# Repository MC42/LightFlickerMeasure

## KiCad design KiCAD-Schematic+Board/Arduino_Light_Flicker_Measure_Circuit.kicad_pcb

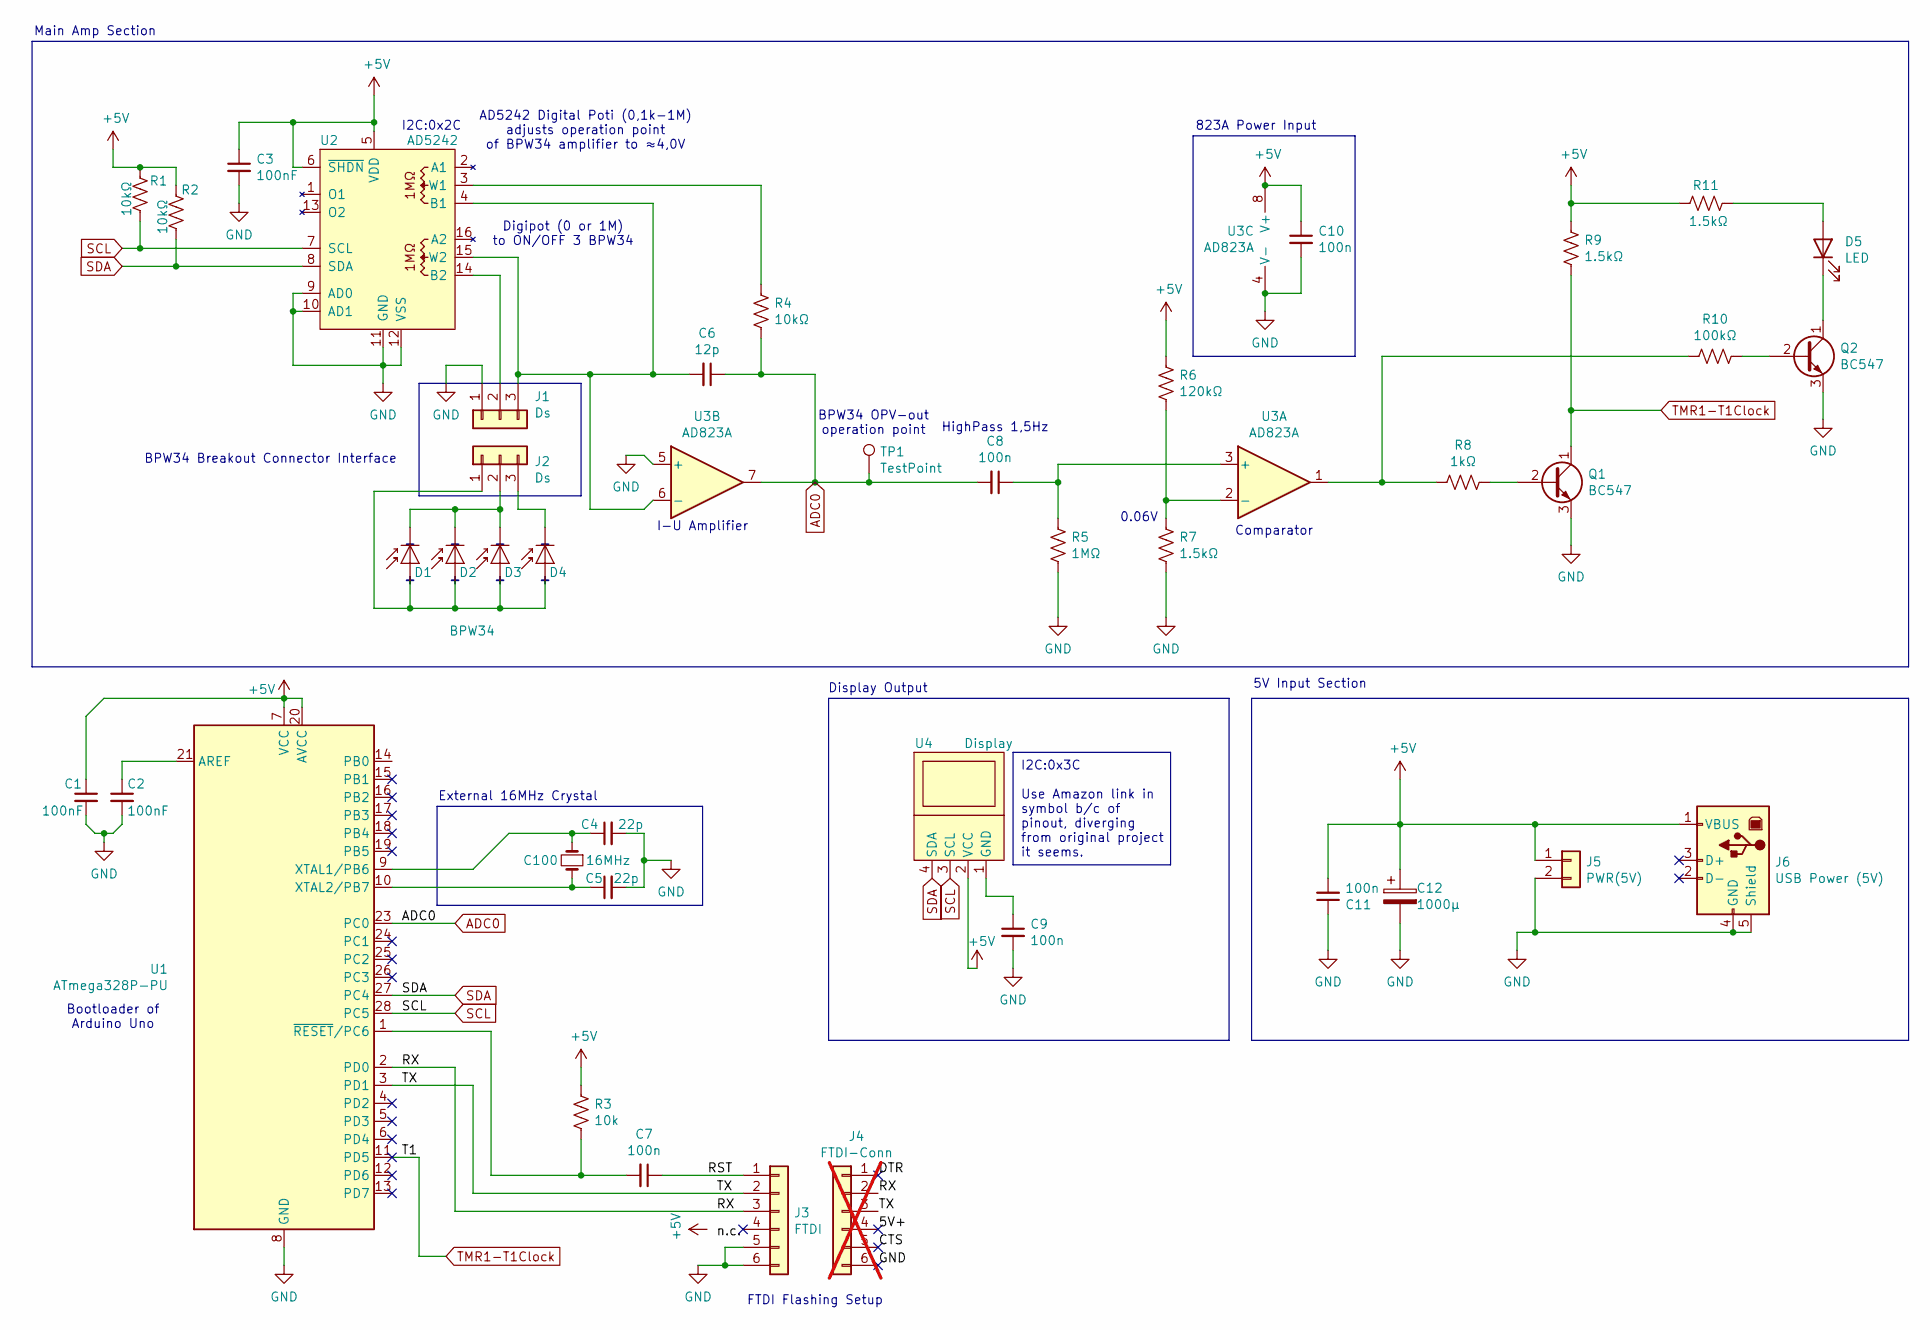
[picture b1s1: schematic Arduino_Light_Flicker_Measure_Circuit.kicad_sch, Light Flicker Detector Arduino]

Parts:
C1, C3: 100nF; C_Rect_L11.0mm_W2.8mm_P10.00mm_MKT
C2: 100nF; C_Rect_L4.0mm_W2.5mm_P2.50mm
C4, C5: 22p; C_Disc_D3.0mm_W1.6mm_P2.50mm
C6: 12p; C_Disc_D3.0mm_W1.6mm_P2.50mm
C7, C10: 100n; C_Rect_L9.0mm_W2.5mm_P7.50mm_MKT
C8: 100n; C_Rect_L7.0mm_W2.0mm_P5.00mm
C9, C11: 100n; C_Rect_L4.0mm_W2.5mm_P2.50mm
C12: 1000µ; CP_Radial_D8.0mm_P3.50mm
C100: 16MHz; Crystal_HC49-U_Vertical
D1, D2, D3, D4: BPW34; Osram_DIL2_4.3x4.65mm_P5.08mm
D5: LED; LED_D3.0mm
J1, J2: Ds; PinHeader_1x03_P2.54mm_Vertical
J3: FTDI; PinHeader_1x06_P2.54mm_Vertical
J4: FTDI-Conn; PinHeader_1x06_P2.54mm_Vertical; not fitted
J5: PWR(5V); PinHeader_1x02_P2.54mm_Vertical
J6: USB Power (5V); USB_A_CNCTech_1001-011-01101_Horizontal
Q1, Q2: BC547; TO-92_HandSolder
R1, R2: 10kΩ; R_Axial_DIN0207_L6.3mm_D2.5mm_P10.16mm_Horizontal
R3: 10k; R_Axial_DIN0207_L6.3mm_D2.5mm_P10.16mm_Horizontal
R4: 10kΩ; R_Axial_DIN0207_L6.3mm_D2.5mm_P10.16mm_Horizontal
R5: 1MΩ; R_Axial_DIN0207_L6.3mm_D2.5mm_P10.16mm_Horizontal
R6: 120kΩ; R_Axial_DIN0207_L6.3mm_D2.5mm_P10.16mm_Horizontal
R7, R9, R11: 1.5kΩ; R_Axial_DIN0207_L6.3mm_D2.5mm_P10.16mm_Horizontal
R8: 1kΩ; R_Axial_DIN0207_L6.3mm_D2.5mm_P10.16mm_Horizontal
R10: 100kΩ; R_Axial_DIN0207_L6.3mm_D2.5mm_P10.16mm_Horizontal
TP1: TestPoint; PinHeader_1x01_P2.54mm_Vertical
U1: ATmega328P-PU; DIP-28_W7.62mm
U2: AD5242; SOIC-16_3.9x9.9mm_P1.27mm
U3: AD823A; SOIC-8_3.9x4.9mm_P1.27mm
U4: Display; PinHeader_1x04_P2.54mm_Vertical

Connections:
+5V: C1.1, C3.1, C10.1, C11.2, C12.1, J5.1, J6.1 (VBUS), R1.1, R2.1, R3.1, R6.1, R9.1, R11.1, U1.7 (VCC), U1.20 (AVCC), U2.5 (VDD), U2.6 (~SHDN), U3.8 (V+), U4.2 (VCC)
/RST: C7.1, J3.1
/RX: J3.3, J4.2, U1.2 (PD0)
/TX: J3.2, J4.3, U1.3 (PD1)
ADC0: C6.1, C8.2, R4.2, TP1.1, U1.23 (PC0), U3.7
GND: C1.2, C2.2, C3.2, C4.2, C5.2, C9.2, C10.2, C11.1, C12.2, J1.1, J3.5, J3.6, J5.2, J6.4 (GND), J6.5 (Shield), Q1.3 (E), Q2.3 (E), R5.2, R7.2, U1.8 (GND), U1.22 (GND), U2.9 (AD0), U2.10 (AD1), U2.11 (GND), U2.12 (VSS), U3.4 (V-), U3.5 (+)
unnamed: D1.2 (A), D2.2 (A), D3.2 (A), D4.2 (A), J2.1
unnamed: D1.1 (K), D2.1 (K), D3.1 (K), J2.2
unnamed: D4.1 (K), J2.3
unnamed: D5.2 (A), R11.2
unnamed: D5.1 (K), Q2.1 (C)
unnamed: J1.2, U2.14 (B2)
unnamed: C6.2, J1.3, U2.4 (B1), U2.15 (W2), U3.6 (-)
unnamed: Q1.2 (B), R8.1
unnamed: Q2.2 (B), R10.1
unnamed: R8.2, R10.2, U3.1
unnamed: C2.1, U1.21 (AREF)
unnamed: C4.1, C100.1, U1.9 (XTAL1/PB6)
unnamed: C5.1, C100.2, U1.10 (XTAL2/PB7)
unnamed: C7.2, R3.2, U1.1 (~RESET/PC6)
unnamed: R4.1, U2.3 (W1)
unnamed: C8.1, R5.1, U3.3 (+)
unnamed: R6.2, R7.1, U3.2 (-)
unnamed: C9.1, U4.1 (GND)
SCL: R1.2, U1.28 (PC5), U2.7 (SCL), U4.3 (SCL)
SDA: R2.2, U1.27 (PC4), U2.8 (SDA), U4.4 (SDA)
TMR1-T1Clock: Q1.1 (C), R9.2, U1.11 (PD5)

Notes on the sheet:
I2C:0x3C Use Amazon link in symbol b/c of pinout, diverging from original project it seems.
823A Power Input
BPW34 Breakout Connector Interface
External 16MHz Crystal
Comparator
Display Output
Main Amp Section
FTDI Flashing Setup
5V Input Section
Bootloader of Arduino Uno
Digipot (0 or 1M) to ON/OFF 3 BPW34
0.06V
I2C:0x2C
AD5242 Digital Poti (0,1k-1M) adjusts operation point of BPW34 amplifier to ≈4,0V
HighPass 1,5Hz
BPW34 OPV-out operation point
I-U Amplifier

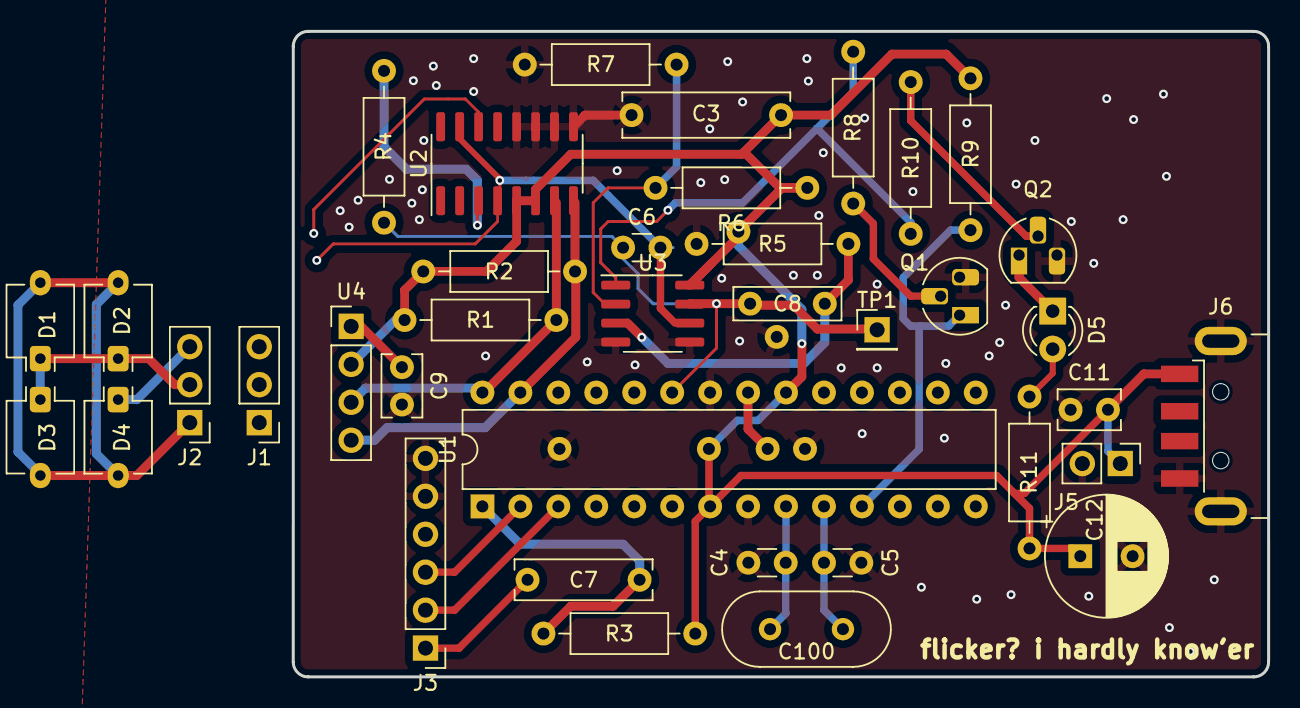
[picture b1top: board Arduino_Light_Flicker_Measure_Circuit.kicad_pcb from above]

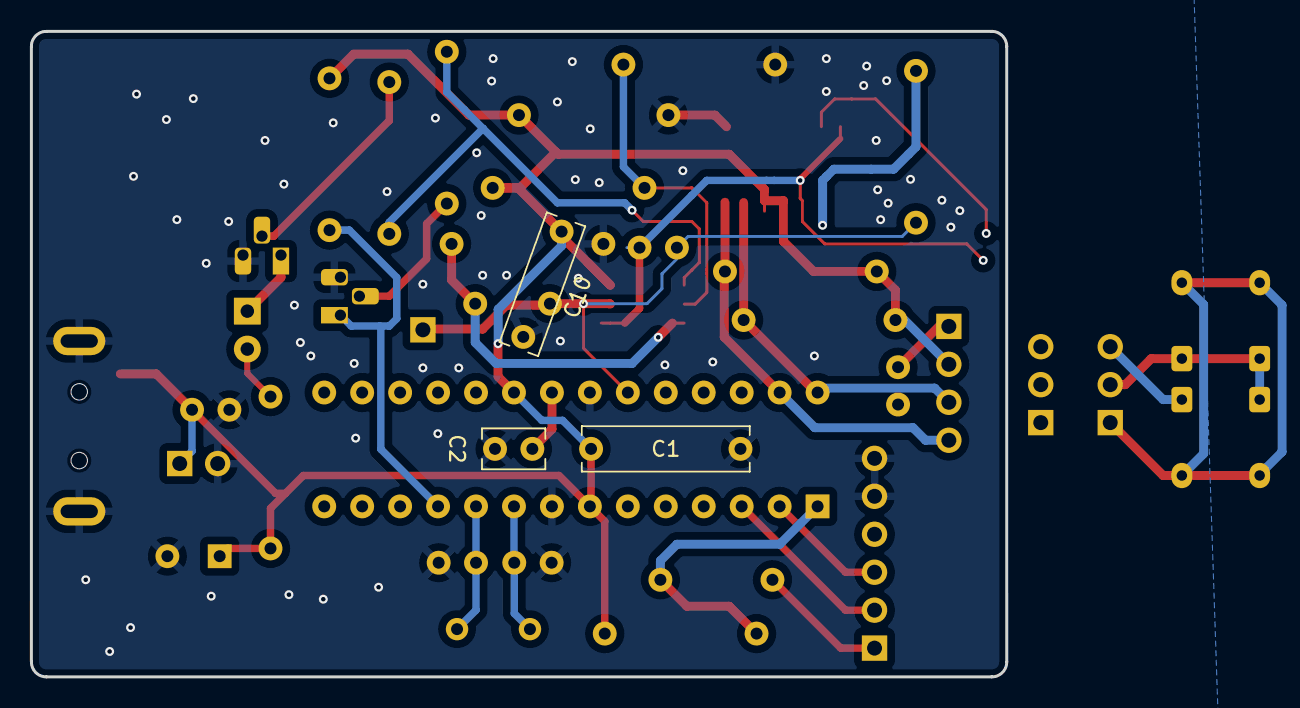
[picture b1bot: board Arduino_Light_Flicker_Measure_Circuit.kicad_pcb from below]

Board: 2 copper layers, 65.3 x 43.2 mm, 41 parts (3 on the bottom side), 27 nets.

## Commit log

2023-10-15 Update to KiCAD 7.99 files and try to fix missing symbols for modern use.
2023-10-15 Add new AD5242 symbol recreation for using it as-is and moved some notation to internal symbol library stuff?
2023-10-15 Add SSD1306 file, minor updates, also swapped two pins. Slowly iterating.
2023-10-15 Update board setup to be mostly complete. Still need to shrink and reorganize a bit.
2023-10-15 ignore backups and update gitignore to exclude them, yay.
2023-10-15 Fix broken gitignore due to typo... Ouch. Also clean up schematic even more, still need to do proper layout and BOM sourcing stuff. Plus figure out the actual parts for the photodiodes still.
2023-10-21 Small update to add Pro Mini footprint to get rid of original footprint stuff hopefully.
2023-11-25 Update to do basic messed-up layout. Imperfect but hopefully functional.

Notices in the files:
KiCAD-Schematic+Board/Arduino_Light_Flicker_Measure_Circuit.kicad_pcb:
GPLv3 OSHW
